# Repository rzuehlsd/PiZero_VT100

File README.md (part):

# VT100 Terminal Emulation on Raspberry Pi Zero W with Circle Bare Metal  Framework

## Table of Contents

- [Motivation](#motivation)
- [Regards](#regards)
- [Current Change Status](#current-change-status-2026-09-29)
- [License Statement](#license-statement)
- [Documentation Policy](#documentation-policy)
- [Software Implementation](#software-implementation)
  - [Scope and Goals](#scope-and-goals)
  - [Main Features](#main-features)
  - [Compile Environment Setup](#compile-environment-setup)
    - [Make Targets](#make-targets)
    - [macOS (tested)](#macos-tested)
    - [Important Note about Homebrew formulas](#important-note-about-homebrew-formulas)
  - [Configuration](#configuration)
    - [Configuration File: VT100.txt](#configuration-file-vt100txt)
    - [Available Options](#available-options)
      - [Configuration Summary](#configuration-summary)
      - [VT100 SETUP Screen A Parameter Mapping](#vt100-setup-screen-a-parameter-mapping-current-status)
      - [VT100 SETUP Screen B Parameter Mapping](#vt100-setup-screen-b-parameter-mapping-current-status)
      - [VT100 Extended Setup Dialog (F11)](#vt100-extended-setup-dialog-f11)
    - [DEC Local Mode (F10)](#dec-local-mode-f10)
    - [Example VT100.txt](#example-vt100txt)
  - [Circle Boot Files](#circle-boot-files)
  - [Display Orientation](#display-orientation)
  - [Debug and Logging](#debug-and-logging)
  - [WLAN Telnet and Host Mode](#wlan-telnet-and-host-mode)
    - [Log mode (WLAN diagnostics)](#log-mode-wlan-diagnostics)
    - [Shell-client mode (outbound raw TCP)](#shell-client-mode-outbound-raw-tcp)
    - [Host-side tooling reference](#host-side-tooling-reference)
    - [Auto-start shell-client mode](#auto-start-shell-client-mode)
    - [Strict mode separation](#strict-mode-separation)
  - [Internal VT100 Test Integration](#internal-vt100-test-integration)
  - [Initial Implementation Plan](#initial-implementation-plan)
  - [Templates](#templates)
  - [Overview on Escape Sequence Coverage](#overview-on-escape-sequence-coverage)
  - [VT100 Conformance Assessment](#vt100-conformance-assessment)
  - [Practical vttest Plan](#practical-vttest-plan)
  - [Troubleshooting](#troubleshooting)
    - [Build fails with stdint.h missing](#build-fails-with-fatal-error-stdinth-no-such-file-or-directory)
    - [VT100.txt changes have no effect](#vt100txt-changes-have-no-effect)
    - [Cannot connect to WLAN telnet console](#cannot-connect-to-wlan-telnet-console)
    - [Telnet shows logs but no shell-client traffic](#connected-via-telnet-but-only-logs-appear-no-shell-client-traffic)
    - [Shell-client uses UART instead of the remote host](#shell-client-mode-enabled-but-vt100-still-follows-uart-host)
    - [screen does not connect directly to TCP](#screen-does-not-connect-directly-to-tcp)
    - [Auto-enter host mode on every connect](#auto-enter-host-mode-on-every-connect)

## Motivation
My main motivation was that I wanted a terminal emulation for my VT100 replica (https://www.instructables.com/23-Scale-VT100-Terminal-Reproduction/) which I printed and assembled. I wanted something that could start within seconds, so a bare metal implementation on a Pi Zero seems to be the way to go. I looked into the PiGFX implementation by Filippo Bergamasco (https://github.com/fbergama/pigfx) and PiVT VT220 Emulator by Hans Hübner (https://github.com/hanshuebner/pivt). PiGFX for my taste was to much focused on reproducing vintage games on Z80 hardware or similar whereas PiVt was focused on VT220 with minimal configurability. Also the support for VT100 features like font stretching, double width fonts and double width double height fonts was missing in both implementations. 
So I decided to start my own VT100 Emulator journay and here is the result.

Below you see the original VT100 terminal (the color has turned to yellow over the years) and my 60% replica in a color that matches the original "oyster white" and some font examples:

<table>
  <tr>
    <td></td>
    <td></td>
  </tr>
  <tr>
    <td></td>
    <td></td>
  </tr>
</table>

The follwing link gives a very good view of the original VT100 from 1079:
- [Pictures of a VT100 from 1979](https://www.artstation.com/artwork/d05JgW)

The current VT100 terminal firmware turns a Raspberry Pi Zero W into a self-contained ANSI/VT100-compatible console. It boots straight into the terminal without Linux, using the Circle bare-metal framework for deterministic hardware access. The design targets headless benches and retro workstations that need a physical keyboard and display front-end for serial hosts.

This project also includes a PCB design to support enhanced features such as a buzzer, an RS-232 adapter, a Mini-DIN-6 adapter for MBC2-Z80, and power distribution for the Pi Zero, MBC2, and display, plus a backplate to mount the board inside a 60% VT100 replica designed by megardi.

My aim was to replicate the behaivior of a true VT100 as close as possible (vttest will show the final result ;-) ) and be able to mimic a VT52, VT220 and my favorite the VT320 in amber, also I did not replicate the small deviations of the VT220 or VT320 font sets. I got the original font definitions for a VT100 font from the ROM data used by Lars Brinkhoff to simulate a VT100 terminal in software on a Pi.

If you want a nearly 100% VT100 terminal simulation, please go for the VT100 simulation from Lars Brinkhoff (https://github.com/larsbrinkhoff/terminal-simulator). He simulates the complete VT100 hardware with original ROMs on a Raspberry Pi. The Pi executes the ROM by an 8080 emulator and simulates other components like video display with character generator ROM, settings NVRAM, Intel 8251 USART, and a keyboard matrix scanner. 

## Regards

Many thanks to Rene Stange (https://github.com/rsta2) for the creation of the Circle bare metal framework for Raspberry Pis. Without his work this project would not have been possible.

I take my hat off to the engineers a DEC which did a terrific job implementing the VT100 based on the technologies available at that time. They squeezed all functionality I implemented on a Pi with 1 GHz frequency and 512MB into a 8080A with 2Mhz, 8kB of ROM (including the original VT100 7x10 font) and 3kB of RAM. Granted, a lot of the features I had to implement in software were done with analog circuits, but I really feel embarressed by their skills.

## Current Change Status (2026-09-29)

- Hardware: the V2.3 design adds a GPIO7-controlled 5 V supply for a DIN6-connected SBC, BSS138 RX/TX level shifters, a 40 V / 2 A bridge rectifier, revised resistor pads, regulator notes, and a top-mount USB-A connector. The V2.3 board has not yet been manufactured or hardware-tested; the GPIO7 power test remains pending.
- Firmware: persistent `sbc_power` (default `0`) is available in the modern F11 setup and is applied at startup and when setup settings are saved with Enter. Setup-dialog behavior has been verified.

## License Statement 
Copyright (C) 2026 Ralf Zühlsdorff

This software and hardware design are released under the MIT License. You may use, copy, modify, merge, publish, distribute, sublicense, and/or sell copies of it, subject to including the copyright notice and permission notice in all copies or substantial portions.

## Documentation Policy

This project keeps documentation in a strict 4-document model:

- This `README.md` document provides the functional overview of the implemented software and user-facing operation guidance.
- [Architecture Overview](VT100/docs/VT100_Architecture.md) is the single technical architecture + implementation reference for developers.
- [Configuration Guide](VT100/docs/Configuration_Guide.md) contains all configuration guidance, split into user/operator and admin/developer parts.
- [Hardware Design](VT100/docs/Hardware.md) contains the KiCad design of the PCB and the OpenSCAD files for printing the backplate.

Generated API documentation is also published via GitHub Pages:

- [Doxygen HTML Documentation](https://rzuehlsd.github.io/PiZero_VT100/)

When implementation changes affect behavior, update these documents in lockstep and avoid introducing additional overlapping technical documents.

# Software Implementation

The application initialises USB keyboard input, the framebuffer, GPIO, UART, and WLAN within Circle and runs a cooperative task loop that keeps the terminal responsive even under heavy serial traffic. Classic aesthetics are preserved by rendering converted VT100 ROM fonts at 1024x768, while modern conveniences such as remote logging remain available.

The current renderer keeps terminal text, attributes, and DEC line-size state primarily in a shadow buffer and then projects that model onto the framebuffer through a dedicated projector task. During active smooth scrolling the projector stays on the incremental region-update path and defers any required catch-up full refresh until the animation completes. This makes state restore, scrolling, insert/delete operations, and external `vttest`-style screen rewrites behave against one consistent terminal model instead of depending on already-drawn pixels.

## Scope and Goals

- Provide a responsive VT100/ANSI terminal experience with integrated keyboard, framebuffer, and UART handling.
- Preserve classic look-and-feel through ROM-derived fonts, colour themes, and optional CRT-style scan lines.
- Offer configurable serial, display, audio, and logging behaviour via both on-device UI and SD-card files.
- Deliver flexible diagnostics through screen, file, and WLAN logging with remote telnet mirroring.
- Keep deployment simple: copy firmware, configuration files, and optional fonts onto an SD card and power the Pi.

## Main Features

- [x] USB keyboard input with Circle keymap support for multiple languages
- [x] Configurable line endings (LF, CRLF, CR)
- [x] Separate `VT100.txt` configuration file on the SD boot partition
- [x] Circle boot configuration via `cmdline.txt` and `config.txt`
- [x] Serial UART interface to host via RS232 and Mini-DIN-6 connector
- [x] Support for TCP/IP host connections
- [x] Framebuffer renderer supporting multiple VT fonts and colour themes
  - [x] DEC VT100 ROM 8x20 with scan-line simulation
  - [x] VT100 10x20 CRT-style font derived from DEC VT100 ROM Font
  - [x] VT100 10x20 solid font derived from DEC VT100 ROM Font
  - [x] DEC VT100 Special Graphics Character Set support (via `ESC ( 0` and `ESC ( B`)
  - [x] Dynamic Double-Width / Double-Height line attributes with DEC top/bottom-half semantics (`ESC #3/#4/#5/#6`)
  - [x] Visible SGR blink text rendering synchronized to the existing cursor blink cadence
  - [x] White, amber, and green on black simulate DEC monochrome terminals (VT100, VT220, VT320)
- [x] VT100 and ANSI escape sequence parser and renderer based on the VT-parse project
- [x] Configurable optional VT52 escape sequence support
- [x] 800 Hz buzzer with configurable volume for bell and key click feedback
- [x] Logging infrastructure with screen, file, and WLAN sinks
  - [x] Real-time debug output with formatted log messages
  - [x] WLAN debug output via telnet session
  - [x] WLAN split between incoming telnet log mode and outbound shell-client mode (current implementation)
  - [x] Shell-client mode can auto-connect from `host_id` or prompt locally for `IPv4[:port]`
  - [x] WLAN logging and shell-client mode successfully validated with local loopback and raw TCP helper tooling
- [x] GPIO16-controlled TX/RX swap to simulate Null Modem cables with straight DB9 cables
- [x] Configuration of system via VT100 Setup Screens A and B for supported parameters
- [x] Separate on-screen setup dialog covering the 24 persisted `VT100.txt` keys implemented there, including `smooth_scroll`, `smooth_scroll_ms`, `host_id`, and SBC power via `sbc_power` / GPIO7 (F11)

The following table gives an overview of implementation highlights:

| Area | Highlights |
| --- | --- |
| **Core Terminal** | ANSI/VT100 parser, ROM-derived fonts, shadow-buffer-first framebuffer renderer with DEC line-size control and visible blink attributes |
| **Input** | USB keyboard with F12 legacy setup, F11 modern setup, F10 local mode toggle, optional key click |
| **Serial** | Configurable UART baud rates, software flow control (XON/XOFF), GPIO16 TX/RX swap |
| **Display & Audio** | Runtime font switching, colour themes, buzzer tones, projector-owned smooth-scroll tuning, periodic status tasks |
| **Configuration** | SD-based `VT100.txt`, Circle `cmdline.txt`/`config.txt`, manual SD-card editing |
| **Logging** | Bitmask-controlled outputs (screen, file, WLAN), telnet console, timestamped files |
| **Networking** | WLAN bring-up with WPA supplicant, telnet banner showing `ip:2323` |
| **Deployment** | Makefile-driven build, SD card copy workflow, optional bootloader assets |

WLAN remote operation test status: WLAN logging mode and outbound shell-client mode have been successfully tested with local loopback and the helper workflows documented in `VT100/tools/README.md`.

And here are the results of the internal tests which could be switched on in VT100.txt config file:

## Compile Environment Setup

### Make Targets

The following table lists the implemented Make targets available from `VT100/Makefile` (including targets inherited via `../Rules.mk`) and their purpose.

| Target | Purpose |
| --- | --- |
| `all` | Default target; builds firmware image and copies it to `VT100/bin/kernel.img`. |
| `kernel.img` | Creates/refreshes local `kernel.img` symlink to `VT100/bin/kernel.img`. |
| `clean` | Removes generated build artifacts (`build/`, intermediate objects, map/list/elf/img outputs). |
| `docs` | Generates Doxygen documentation from `VT100/Doxyfile` into `VT100/docs/doxygen/`. |
| `docs_clean` | Removes generated Doxygen output directories/files under `VT100/docs/doxygen/`. |

This project needs a **complete bare-metal Arm GNU toolchain** (compiler + target C library headers like `stdint.h`).

### macOS (tested)

Install required host tools and the full Arm toolchain:

```bash
brew install make
brew install --cask gcc-arm-embedded
```

Configure Circle to use the full toolchain path explicitly:

```bash
cd /Users/ralf/Projekte/VT100_Circle
./configure -f -p /Applications/ArmGNUToolchain/15.2.rel1/arm-none-eabi/bin/arm-none-eabi-
```

Verify the compiler and header availability:

```bash
/Applications/ArmGNUToolchain/15.2.rel1/arm-none-eabi/bin/arm-none-eabi-gcc --version
printf '#include <stdint.h>\nint main(void){return 0;}\n' | \
    /Applications/ArmGNUToolchain/15.2.rel1/arm-none-eabi/bin/arm-none-eabi-gcc -x c - -c -o /tmp/vt100_stdint_test.o
```

Build steps:

```bash
cd /Users/ralf/Projekte/VT100_Circle
./makeall
cd VT100
make -j4
```

### Important Note about Homebrew formulas

The Homebrew formula `arm-none-eabi-gcc` may be built without target headers (`--without-headers`), which can cause errors like `fatal error: stdint.h: No such file or directory`. The `gcc-arm-embedded` cask provides the complete toolchain required by this project.

## Configuration

The VT100 terminal reads configuration from `VT100.txt` on the SD boot partition and supplements it with Circle boot parameters in `cmdline.txt` and firmware settings in `config.txt`/`config64.txt`.

### Configuration File: VT100.txt

Create or edit `VT100.txt` on the boot partition. The firmware loads it on startup, and settings can be changed either by manual edits or via the on-screen setup dialogs (F11/F12). See [VT100/bin/VT100.txt](VT100/bin/VT100.txt) for the shipping template.

### Available Options

#### Configuration Summary

| Key | Allowed values | Default | Notes |
| --- | --------------- | ------- | ----- |
| `baud_rate` | 50–921600 | 115200 | Host serial speed |
| `serial_bits` | 7/8 | 8 | UART data bits (SET-UP B Bits/Char) |
| `serial_parity` | 0–2 | 0 | UART parity (0=none, 1=even, 2=odd) |
| `background_color` | 0–3 | 0 | Palette: 0=black, 1=white, 2=amber, 3=green |
| `buzzer_volume` | 0–80 | 50 | Sets 800 Hz buzzer duty cycle (0 disables tone; values above 80 are clamped) |
| `cursor_blinking` | 0/1 | 0 | 1 enables blink animation |
| `cursor_type` | 0/1 | 0 | Cursor style (0=underline, 1=block) |
| `key_auto_repeat` | 0/1 | 1 | Enables or disables keyboard auto-repeat |
| `vt_test` | 0/1 | 0 | Run built-in VT test sequences |
| `vt52_mode` | 0/1 | 0 | Terminal mode: 0=ANSI (VT100), 1=VT52 |
| `font_selection` | 1–3 | 2 | Choose between 8x20, 10x20 CRT, 10x20 solid |
| `flow_control` | 0/1 | 0 | Software XON/XOFF UART flow control |
| `key_click` | 0/1 | 1 | Enables or disables key click feedback |
| `line_ending` | 0–2 | 0 | Enter key behaviour: 0=LF, 1=CRLF, 2=CR |
| `host_id` | String (IPv4[:port]) | empty | Default shell-client target used when `wlan_host_autostart=2` |
| `log_filename` | String (≤63 chars) | vt100.log | Used when file logging is active |
| `log_output` | 0–7 | 0 | 0=off, 1=screen, 2=file, 3=WLAN, 4=screen+file, 5=screen+WLAN, 6=file+WLAN, 7=all |
| `smooth_scroll` | 0/1 | 1 | Enables non-blocking smooth single-line scroll animation |
| `smooth_scroll_ms` | 10–500 | 170 | Sets the target duration per scrolled text line |
| `wrap_around` | 0/1 | 1 | Controls right-margin wrap (`1`) vs overwrite-at-last-column (`0`) |
| `repeat_delay_ms` | 250–1000 | 250 | Delay before auto-repeat starts |
| `repeat_rate_cps` | 2–20 | 10 | Characters per second once repeating |
| `margin_bell` | 0/1 | 0 | Rings bell 8 columns before right margin when enabled |
| `switch_txrx` | 0/1 | 0 | Drives GPIO16 high to swap wiring |
| `wlan_host_autostart` | 0–2 | 0 | Current implementation policy: 0=off, 1=log mode, 2=outbound shell-client mode |
| `text_color` | 0–3 | 1 | Foreground palette: 0=black, 1=white, 2=amber, 3=green |

On-screen configuration is available through the VT100 SET-UP dialogs A and B, opened with `F12`, and through an extended configuration dialog opened with `F11`. The extended dialog covers 23 persisted `VT100.txt` keys plus the runtime-applied visual settings; `flow_control`, `wrap_around`, and `margin_bell` remain on the legacy VT100-style `F12` path.

#### VT100 SETUP Screen A Parameter Mapping (current status)

The table below maps the current SET-UP A screen controls to firmware behavior.

| SET-UP A item | Corresponding config/runtime state | Implementation status |
| --- | --- | --- |
| Horizontal tab stops (per column) | Runtime tab-stop map via `CTConfig::SetTabStop()` / `CTConfig::IsTabStop()` | Implemented |
| Cursor movement in ruler (`Left`, `Right`, `Home`, `End`) | Tab edit cursor in SET-UP A ruler line | Implemented |
| Set/clear tab at current column (`T` / space) | Updates tab stop at current column | Implemented |
| Tab-stop persistence in `VT100.txt` | Not mapped to persisted file keys yet | Not implemented |

#### VT100 SETUP Screen B Parameter Mapping (current status)

The table below maps original VT100 SET-UP B terms to the current firmware configuration model.

| Tab group | Parameter name (VT100 docs) | Corresponding config param | Implementation status |
| --- | --- | --- | --- |
| 1 | Scroll | `smooth_scroll` (leftmost bit in group 1, mask `0x8`) | Implemented |
| 1 | Auto Repeat | `key_auto_repeat` (+ `repeat_delay_ms`, `repeat_rate_cps`) | Implemented |
| 1 | Screen | runtime-only (`screen_inverted`, not persisted) | Implemented |
| 1 | Cursor | `cursor_type` | Implemented |
| 2 | Bell | `margin_bell` (group 2 leftmost bit, mask `0x8`) | Implemented |
| 2 | Keyclick | `key_click` | Implemented |
| 2 | ANSI/VT52 | `vt52_mode` | Implemented |
| 2 | Auto XON/XOFF | `flow_control` (group 2 rightmost shown bit, mask `0x1`) | Implemented |
| 3 | US/UK # | N/A | Not implemented |
| 3 | Wraparound | `wrap_around` (group 3 second bit from left, mask `0x4`) | Implemented |
| 3 | New Line | `line_ending` | Implemented |
| 3 | Interlace | N/A | Not implemented |
| 4 | Parity Sense | `serial_parity` (1=even, 2=odd when parity enabled) | Implemented |
| 4 | Parity | `serial_parity` (0=none, 1/2=enabled) | Implemented |
| 4 | Bits/Char | `serial_bits` (7/8) | Implemented |
| 4 | Power | N/A | Not implemented |
| — | T SPEED (Transmit Speed) | `baud_rate` | Implemented |
| — | R SPEED (Receive Speed) | Follows `baud_rate` (TX speed) | Always follows transmit speed |

#### VT100 Extended Setup Dialog (F11)

Press `F11` to open the extended setup dialog. The dialog uses DEC special graphics box drawing, keeps the active terminal color/font theme, uses a centered normal-width title, and shows a three-column `parameter` / `value` / `description` view for the 23 persisted `VT100.txt` keys exposed there, including `smooth_scroll`, `smooth_scroll_ms`, and `host_id`. The remaining persisted keys `flow_control`, `wrap_around`, and `margin_bell` stay mapped to the VT100-compatible `F12` setup flow. Before the overlay takes over the screen, the renderer aborts any active smooth-scroll animation and forces a stable projector refresh so the dialog always starts from a complete framebuffer state. Press `F12` for the legacy VT100 setup screens; their title renders as a true two-line DEC double-height header with `TO EXIT PRESS "SET-UP"` directly below it, matching the original VT100 layout more closely.

Controls:

- `Up` / `Down`: select parameter row
- `Left` / `Right`: change selected value
- `Return`: save to runtime + `VT100.txt` and exit
- `Esc`: cancel changes and exit

Runtime apply on `Return` (current firmware):

- Immediate runtime apply: renderer visuals (`text_color`, `background_color`, `font_selection`, cursor type/blink, VT52 mode, `smooth_scroll`, `smooth_scroll_ms`) and HAL settings (`buzzer_volume`, `switch_txrx`).
- Persisted and used by runtime logic without dedicated re-init: `line_ending`, `key_click`, `key_auto_repeat`.
- Persisted (applied on subsystem init / reconnect / reboot): serial framing (`baud_rate`, `serial_bits`, `serial_parity`), keyboard repeat timing (`repeat_delay_ms`, `repeat_rate_cps`), logging targets (`log_output`, `log_filename`), and WLAN host settings (`wlan_host_autostart`, `host_id`).
- Persisted legacy-setup-only keys: `flow_control`, `wrap_around`, and `margin_bell` are edited through `F12`, not through the modern `F11` table.
- While a setup dialog is visible, cooked and raw keyboard events are routed into `CTSetup`, queued in a small FIFO, and then processed in the setup task context so redraws remain stable even when the shell-client connection is active.

### DEC Local Mode (F10)

The DEC feature to toggle the terminal between local (not connected to host) and line (connected to host) mode can be triggered by pressing `F10`.

- `ON`: keyboard input is looped directly to the renderer (local echo), and host output is not sent over UART/TCP.
- `OFF`: keyboard input follows the normal host path again.

The terminal prints a short status line (`VT100 local mode ON/OFF`) when toggled.

### Example VT100.txt

Most of the configurations can be defined in the file VT100.txt on the root volume of the boot SD. The following sections give a summary:

```ini
# VT100 Terminal Configuration File
# Place this file as VT100.txt on the SD card boot partition.
# Values below match firmware defaults.

# --- Serial communication ---
# Host serial speed in bits per second
baud_rate=115200

# UART framing:
# serial_bits: 7 or 8
# serial_parity: 0=None, 1=Even, 2=Odd
serial_bits=8
serial_parity=0

# --- Keyboard / line handling ---
# line_ending: 0=LF, 1=CRLF, 2=CR
line_ending=0

# key_auto_repeat: 0=off, 1=on
key_auto_repeat=1

# smooth_scroll: 0=off, 1=on
smooth_scroll=1

# smooth_scroll_ms: 10..500 milliseconds per text line
smooth_scroll_ms=170

# wrap_around: 0=overwrite at last column, 1=wrap to next line
wrap_around=1

# flow_control: 0=off, 1=software XON/XOFF
flow_control=0

# Delay before repeat starts (milliseconds: 250..1000)
repeat_delay_ms=250

# Repeat rate (characters per second: 2..20)
repeat_rate_cps=10

# key_click: 0=off, 1=on
key_click=1

# --- Terminal mode / display ---
# vt52_mode: 0=ANSI (VT100), 1=VT52
vt52_mode=0

# cursor_type: 0=underline, 1=block
cursor_type=0

# cursor_blinking: 0=steady, 1=blinking
cursor_blinking=0

# vt_test: 0=off, 1=on
vt_test=0

# font_selection: 1=8x20, 2=10x20 CRT, 3=10x20 solid
font_selection=2

# Palette indices: 0=black, 1=white, 2=amber, 3=green
text_color=1
background_color=0

# --- Sound / wiring ---
# buzzer_volume: 0..80 (percent duty cycle)
buzzer_volume=50

# margin_bell: 0=off, 1=ring 8 columns before right margin
margin_bell=0

# switch_txrx: 0=normal wiring, 1=swapped via GPIO16
switch_txrx=0

# --- Logging ---
# log_output:
# 0=off
# 1=screen
# 2=file
# 3=wlan
# 4=screen+file
# 5=screen+wlan
# 6=file+wlan
# 7=screen+file+wlan
log_output=0

# wlan_host_autostart: 0=off, 1=remote log mode, 2=outbound shell-client mode
wlan_host_autostart=0

# host_id: default shell-client target when wlan_host_autostart=2
# Format: IPv4[:port] (e.g. 192.168.2.10 or 192.168.2.10:2323). Leave empty to prompt.
host_id=

# Log file name (max 63 chars)
log_filename=vt100.log
```

## Circle Boot Files

- `cmdline.txt` — Parsed by Circle during boot. Keep options on one line, e.g. `logdev=tty1 loglevel=4 width=1024 height=768 keymap=DE`.
- `config.txt` / `config64.txt` — Raspberry Pi firmware settings. The template applies `dtoverlay=miniuart-bt`, `enable_uart=1`, and `display_hdmi_rotate=2` for the upside-down LCD in the replica enclosure.

Both templates live in `VT100/bin` alongside the firmware image and WLAN support files.

## Display Orientation

In the 60% VT100 replica, depending on the specific model used, the 1024x768 LCD can hide part of the first line and the left-most characters behind the bezel when mounted in the natural orientation. Mounting the panel upside down resolves the mechanical clearance issue. Rotate the output by 180° by adding the following firmware setting to the active `config.txt`/`config64.txt`:

```ini
display_hdmi_rotate=2
```

This rotates the HDMI output 180° at the firmware level so the framebuffer keeps its normal coordinate system without extra rendering adjustments.

## Debug and Logging

The terminal ships with a logging subsystem that mirrors messages to any combination of screen, SD card file, and WLAN telnet session:

- Smart fallback selects a working sink during early boot and transitions seamlessly once the framebuffer is ready.
- Messages use familiar prefixes (`[NOTE]`, `[WARN]`, `[ERROR]`) with file/line metadata to simplify troubleshooting.
- Screen logging integrates with the terminal view without breaking VT100 escape handling.
- WLAN logging announces readiness with `WLAN ready: telnet <ip>:2323`; connect via telnet to monitor remotely.
- Outbound shell-client integration over raw TCP is available for host-side helpers and interactive shells.

Refer to `VT100/docs/VT100_Architecture.md` for technical architecture and implementation details, and `VT100/docs/Configuration_Guide.md` for runtime controls and configuration.

For the architecture and lifecycle model of WLAN log mode and host mode separation, see `VT100/docs/VT100_Architecture.md` (section 8.3).
For host-side helper scripts and character-mode client recommendations, see `VT100/tools/README.md`.

## WLAN Telnet and Host Mode

This firmware currently supports two WLAN behaviors that share the same raw TCP port (`2323`) but serve different roles:

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
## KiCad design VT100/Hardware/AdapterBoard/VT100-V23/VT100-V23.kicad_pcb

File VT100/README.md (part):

# VT100 Terminal Emulation on Raspberry Pi Zero W with Circle Bare Metal  Framework

## Motivation
My main motivation was that I wanted a terminal emulation for my VT100 replica (https://www.instructables.com/23-Scale-VT100-Terminal-Reproduction/) which I printed and assembled. I wanted something that could start within seconds, so a bare metal implementation on a Pi Zero seems to be the way to go. I looked into the PiGFX implementation by Filippo Bergamasco (https://github.com/fbergama/pigfx) and PiVT VT220 Emulator by Hans Hübner (https://github.com/hanshuebner/pivt). PiGFX for my taste was to much focused on reproducing vintage games on Z80 hardware or similar whereas PiVt was focused on VT220 with minimal configurability. Also the support for VT100 features like font stretching, double width fonts and double width double height fonts was missing in both implementations. 
So I decided to start my own VT100 Emulator journay and here is the result.

Below you see the original VT100 terminal (the color has turned to yellow over the years) and my 60% replica in a color that matches the original "oyster white" and some font examples:

<table>
  <tr>
    <td></td>
    <td></td>
  </tr>
  <tr>
    <td></td>
    <td></td>
  </tr>
</table>

The current VT100 terminal firmware turns a Raspberry Pi Zero W into a self-contained ANSI/VT100-compatible console. It boots straight into the terminal without Linux, using the Circle bare-metal framework for deterministic hardware access. The design targets headless benches and retro workstations that need a physical keyboard and display front-end for serial hosts.

This project also includes a PCB design to support enhanced features such as a buzzer, an RS-232 adapter, a Mini-DIN-6 adapter for MBC2-Z80, and power distribution for the Pi Zero, MBC2, and display, plus a backplate to mount the board inside a 60% VT100 replica designed by megardi.

My aim was to replicate the behaivior of a true VT100 as close as possible (vttest will show the final result ;-) ) and be able to mimic a VT52, VT220 and my favorite the VT320 in amber, also I did not replicate the small deviations of the VT220 or VT320 font sets. I got the original font definitions for a VT100 font from the ROM data used by Lard Brinkhoff to simulate a VT100 terminal in software on a Pi.

If you want a nearly 100% VT100 terminal simulation, please go for the VT100 simulation from Lars Brinkhoff (https://github.com/larsbrinkhoff/terminal-simulator). He simulates the complete VT100 hardware with original ROMs on a Raspberry Pi. The Pi executes the ROM by an 8080 emulator and simulates other components like video display with character generator ROM, settings NVRAM, Intel 8251 USART, and a keyboard matrix scanner. 

## Regards

Many thanks to Rene Stange (https://github.com/rsta2) for the creation of the Circle bare metal framework for Raspberry Pis. Without his work this project would not have been possible.

I take my hat off to the engineers a DEC which did a terrific job implementing the VT100 based on the technologies available at that time. They squeezed all functionality I implemented on a Pi with 1 GHz frequency and 512MB into a 8080A with 2Mhz, 8kB of ROM (including the original VT100 7x10 font) and 3kB of RAM. Granted, a lot of the features I had to implement in software were done with analog circuits, but I really feel embarressed by their skills.

## License Statement 
Copyright (C) 2026 Ralf Zühlsdorff

This software and hardware design are released under the MIT License. You may use, copy, modify, merge, publish, distribute, sublicense, and/or sell copies of it, subject to including the copyright notice and permission notice in all copies or substantial portions.

## Documentation Policy

This project keeps documentation in a strict 4-document model:

- This `README.md` document provides the functional overview of the implemented software and user-facing operation guidance.
- [Architecture Overview](docs/VT100_Architecture.md) is the single technical architecture + implementation reference for developers.
- [Configuration Guide](docs/Configuration_Guide.md) contains all configuration guidance, split into user/operator and admin/developer parts.
- [Hardware Design](docs/Hardware.md) contains the KiCad design of the PCB and the OpenSCAD files for printing the backplate.

When implementation changes affect behavior, update these documents in lockstep and avoid introducing additional overlapping technical documents.

# Software Implementation

The application initialises USB keyboard input, the framebuffer, GPIO, UART, and WLAN within Circle and runs a cooperative task loop that keeps the terminal responsive even under heavy serial traffic. Classic aesthetics are preserved by rendering converted VT100 ROM fonts at 1024x768, while modern conveniences such as remote logging remain available.

## Scope and Goals

- Provide a responsive VT100/ANSI terminal experience with integrated keyboard, framebuffer, and UART handling.
- Preserve classic look-and-feel through ROM-derived fonts, colour themes, and optional CRT-style scan lines.
- Offer configurable serial, display, audio, and logging behaviour via both on-device UI and SD-card files.
- Deliver flexible diagnostics through screen, file, and WLAN logging with remote telnet mirroring.
- Keep deployment simple: copy firmware, configuration files, and optional fonts onto an SD card and power the Pi.

## Main Features

- [x] USB keyboard input with Circle keymap support for multiple languages
- [x] Configurable line endings (LF, CRLF, CR)
- [x] Separate `VT100.txt` configuration file on the SD boot partition
- [x] Circle boot configuration via `cmdline.txt` and `config.txt`
- [x] Serial UART interface to host via RS232 and Mini-DIN-6 connector
- [x] Support for TCP/IP host connections
- [x] Framebuffer renderer supporting multiple VT fonts and colour themes
  - [x] DEC VT100 ROM 8x20 with scan-line simulation
  - [x] VT100 10x20 CRT-style font derived from DEC VT100 ROM Font
  - [x] VT100 10x20 solid font derived from DEC VT100 ROM Font
  - [x] DEC VT100 Special Graphics Character Set support (via `ESC ( 0` and `ESC ( B`)
  - [x] Dynamic Double-Width / Double-Height glyph scaling for all fonts
  - [x] White, amber, and green on black simulate DEC monochrome terminals (VT100, VT220, VT320)
- [x] VT100 and ANSI escape sequence parser and renderer based on the VT-parse project
- [x] Configurable optional VT52 escape sequence support
- [x] 800 Hz buzzer with configurable volume for bell and key click feedback
- [x] Logging infrastructure with screen, file, and WLAN sinks
  - [x] Real-time debug output with formatted log messages
  - [x] WLAN debug output via telnet session
  - [x] WLAN host mode to integrate remote hosts via tcp/ip
- [x] GPIO16-controlled TX/RX swap to simulate Null Modem cables with straight DB9 cables
- [x] Configuration of system via VT100 Setup Screens A and B for supported parameters
- [x] Separate on-screen setup dialog covering all file-based configuration parameters (F11)

The following table gives an overview of implementation highlights:

| Area | Highlights |
| --- | --- |
| **Core Terminal** | ANSI/VT100 parser, ROM-derived fonts, framebuffer renderer with cursor control |
| **Input** | USB keyboard with F12 legacy setup, F11 modern setup, F10 local mode toggle, optional key click |
| **Serial** | Configurable UART baud rates, software flow control (XON/XOFF), GPIO16 TX/RX swap |
| **Display & Audio** | Runtime font switching, colour themes, buzzer tones, periodic status tasks |
| **Configuration** | SD-based `VT100.txt`, Circle `cmdline.txt`/`config.txt`, manual SD-card editing |
| **Logging** | Bitmask-controlled outputs (screen, file, WLAN), telnet console, timestamped files |
| **Networking** | WLAN bring-up with WPA supplicant, telnet banner showing `ip:2323` |
| **Deployment** | Makefile-driven build, SD card copy workflow, optional bootloader assets |

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
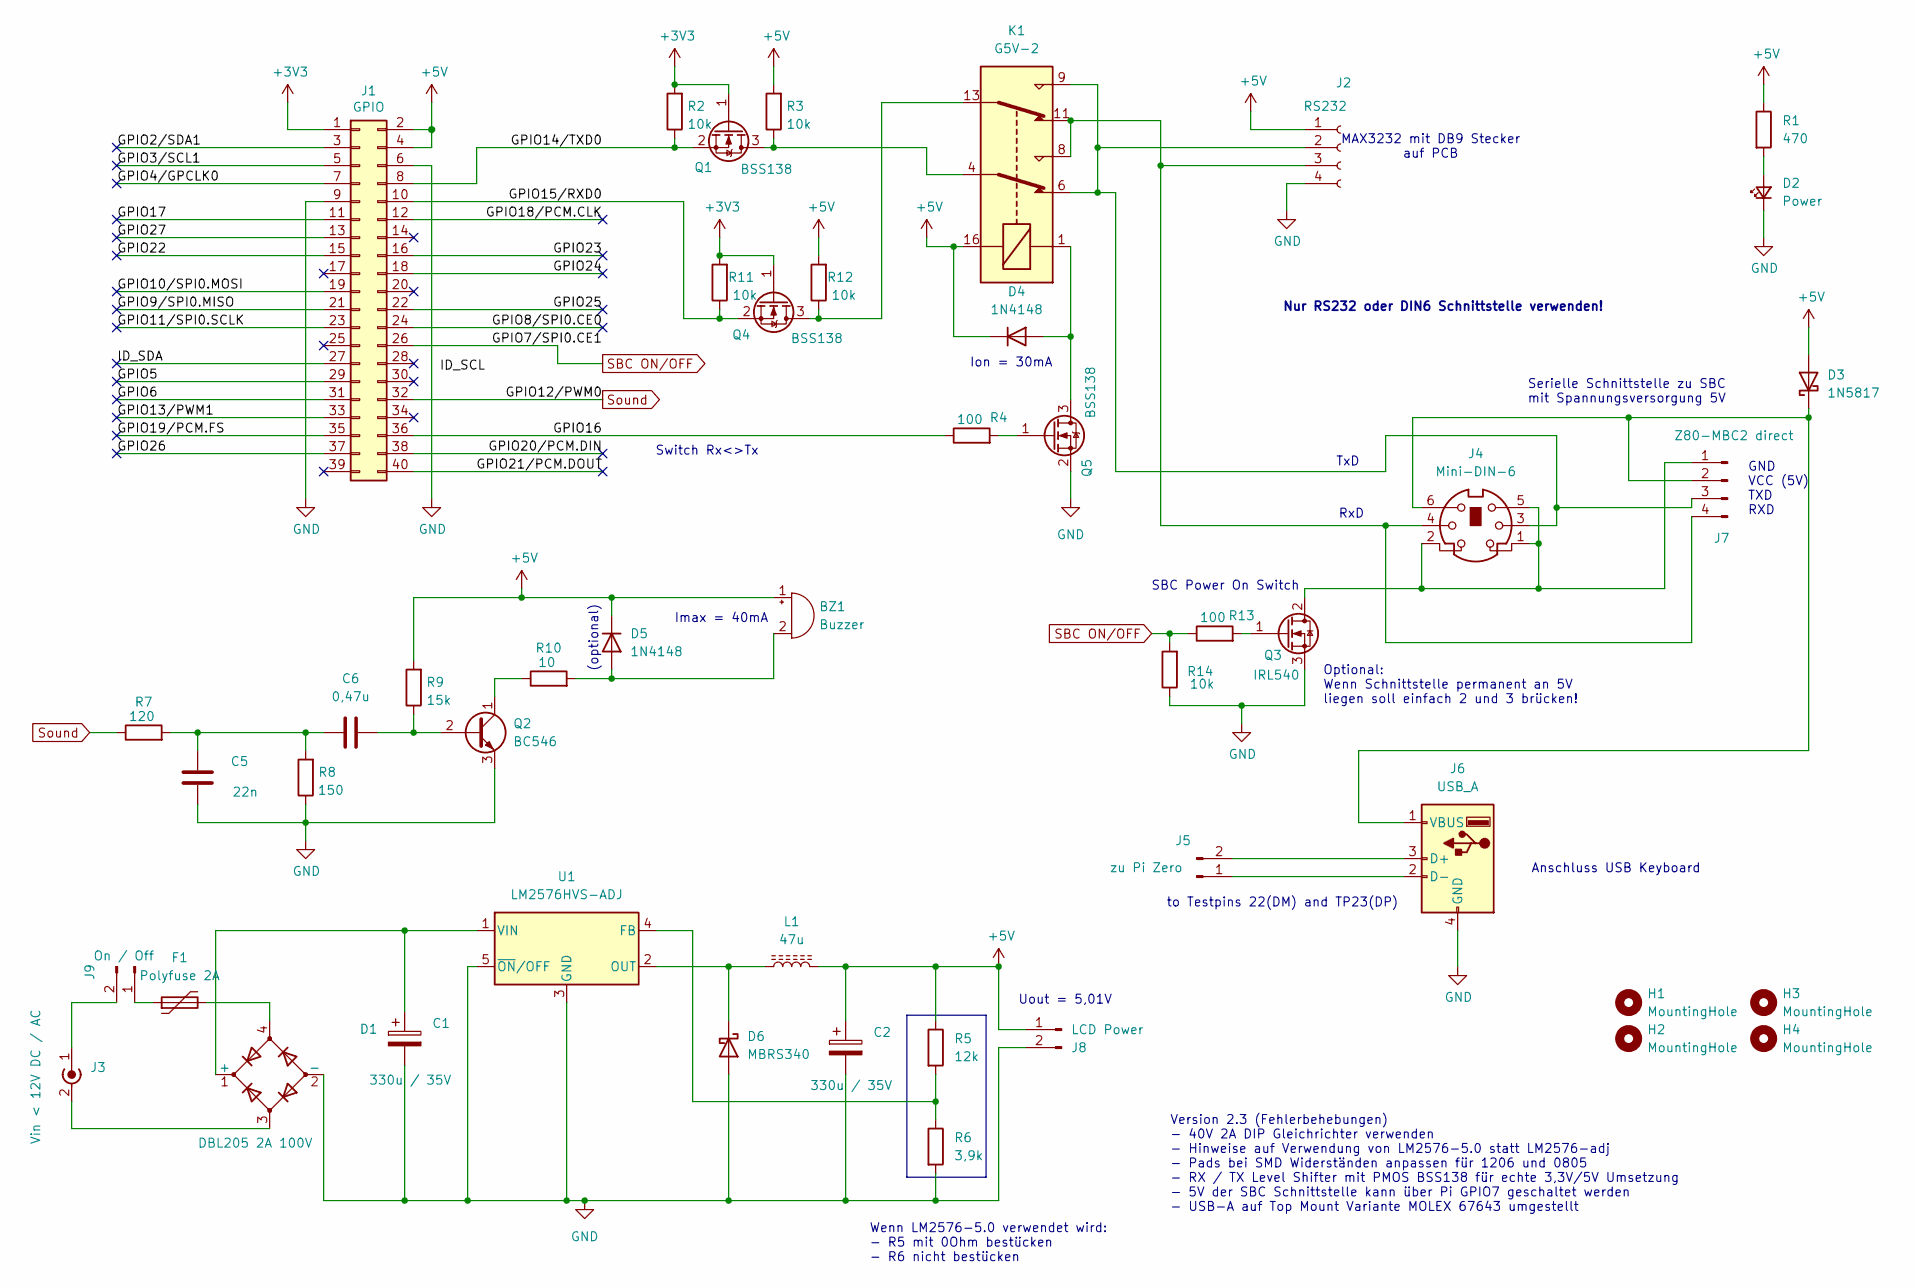
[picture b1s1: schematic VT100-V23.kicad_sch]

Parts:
BZ1: Buzzer; MagneticBuzzer_ProSignal_ABI-009-RC
C1, C2: 330u / 35V; CP_Elec_10x10
C5: 22n; C_0805_2012Metric_Pad1.18x1.45mm_HandSolder
C6: 0,47u; C_0805_2012Metric_Pad1.18x1.45mm_HandSolder
D1: DBL205 2A 100V; Diode_Bridge_DIP-4_W7.62mm_P5.08mm
D2: Power; LED_D3.0mm
D3: 1N5817; D_DO-15_P12.70mm_Horizontal
D4, D5: 1N4148; D_A-405_P10.16mm_Horizontal
D6: MBRS340; D_SMC
F1: Polyfuse 2A; Fuse_Littelfuse-LVR200
H1, H2, H3, H4: MountingHole; MountingHole_3.2mm_M3
J1: GPIO; PinSocket_2x20_P2.54mm_Vertical
J2: RS232; PinSocket_1x04_P2.54mm_Vertical
J3: Vin < 12V DC / AC; BarrelJack_GCT_DCJ200-10-A_Horizontal
J4: Mini-DIN-6; J_Mini-DIN-6
J5: zu Pi Zero; PinHeader_1x02_P2.54mm_Vertical
J6: USB_A; USB_A_Molex_67643_Horizontal
J7: Z80-MBC2 direct; PinHeader_1x04_P2.54mm_Vertical
J8: LCD Power; PinHeader_1x02_P2.54mm_Vertical
J9: On / Off; PinHeader_1x02_P2.54mm_Vertical
K1: G5V-2; Relay_DPDT_Omron_G5V-2
L1: 47u; L_Fastron_PISN
Q1, Q4, Q5: BSS138; SOT-23
Q2: BC546; TO-92_Wide
Q3: IRL540; TO-220-3_Vertical
R1: 470; R_Axial_DIN0207_L6.3mm_D2.5mm_P10.16mm_Horizontal
R2, R3, R11, R12, R14: 10k; R_0805_2012Metric_Pad1.20x1.40mm_HandSolder
R4, R13: 100; R_0805_2012Metric_Pad1.20x1.40mm_HandSolder
R5: 12k; R_1206_3216Metric_Pad1.30x1.75mm_HandSolder
R6: 3,9k; R_1206_3216Metric_Pad1.30x1.75mm_HandSolder
R7: 120; R_0805_2012Metric_Pad1.20x1.40mm_HandSolder
R8: 150; R_0805_2012Metric_Pad1.20x1.40mm_HandSolder
R9: 15k; R_0805_2012Metric_Pad1.20x1.40mm_HandSolder
R10: 10; R_0805_2012Metric_Pad1.20x1.40mm_HandSolder
U1: LM2576HVS-ADJ; TO-263-5_TabPin3

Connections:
+3V3: J1.1, Q1.1 (G), Q4.1 (G), R2.2, R11.2
+5V: BZ1.1 (+), C2.1, D3.2 (A), D4.1 (K), D5.1 (K), J1.2, J1.4, J2.1, J8.1, K1.16, L1.2, R1.1, R3.2, R5.1, R9.2, R12.2
/GPIO2/SDA1: J1.3
/GPIO3/SCL1: J1.5
/GPIO4/GPCLK0: J1.7
/GPIO5: J1.29
/GPIO6: J1.31
/GPIO8/SPI0.CE0: J1.24
/GPIO9/SPI0.MISO: J1.21
/GPIO10/SPI0.MOSI: J1.19
/GPIO11/SPI0.SCLK: J1.23
/GPIO13/PWM1: J1.33
/GPIO14/TXD0: J1.8, Q1.2 (S), R2.1
/GPIO15/RXD0: J1.10, Q4.2 (S), R11.1
/GPIO16: J1.36, R4.1
/GPIO17: J1.11
/GPIO18/PCM.CLK: J1.12
/GPIO19/PCM.FS: J1.35
/GPIO20/PCM.DIN: J1.38
/GPIO21/PCM.DOUT: J1.40
/GPIO22: J1.15
/GPIO23: J1.16
/GPIO24: J1.18
/GPIO25: J1.22
/GPIO26: J1.37
/GPIO27: J1.13
/ID_SDA: J1.27
GND: C1.2, C2.2, C5.2, D1.2 (-), D2.1 (K), D6.2 (A), J1.6, J1.9, J2.4, J6.4 (GND), J8.2, Q2.3 (E), Q3.3 (S), Q5.2 (S), R6.2, R8.1, R14.1, U1.3 (GND), U1.5 (~ON/OFF)
unnamed: BZ1.2 (-), D5.2 (A), R10.2
unnamed: C5.1, C6.1, R7.2, R8.2
unnamed: C1.1, D1.1 (+), U1.1 (VIN)
unnamed: D1.4, F1.2
unnamed: D2.2 (A), R1.2
unnamed: D3.1 (K), J4.6, J6.1 (VBUS), J7.2
unnamed: D4.2 (A), K1.1, Q5.3 (D)
unnamed: D6.1 (K), L1.1, U1.2 (OUT)
unnamed: J2.2, J4.3, J7.3, K1.6, K1.9
unnamed: J2.3, J4.4, J7.4, K1.8, K1.11
unnamed: D1.3, J3.2 (Ext)
unnamed: J3.1 (In), J9.2
unnamed: J5.1, J6.2 (D-)
unnamed: J5.2, J6.3 (D+)
unnamed: J4.1, J4.2, J4.5, J7.1, Q3.2 (D)
unnamed: F1.1, J9.1
unnamed: K1.4, Q1.3 (D), R3.1
unnamed: C6.2, Q2.2 (B), R9.1
unnamed: Q2.1 (C), R10.1
unnamed: Q3.1 (G), R13.2
unnamed: K1.13, Q4.3 (D), R12.1
unnamed: Q5.1 (G), R4.2
unnamed: R5.2, R6.1, U1.4 (FB)
SBC ON/OFF: J1.26, R13.1, R14.2
Sound: J1.32, R7.1

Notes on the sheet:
Imax = 40mA
TxD
RxD
Wenn LM2576-5.0 verwendet wird: - R5 mit 0Ohm bestücken - R6 nicht bestücken
Version 2.3 (Fehlerbehebungen) - 40V 2A DIP Gleichrichter verwenden - Hinweise auf Verwendung von LM2576-5.0 statt LM2576-adj - Pads bei SMD Widerständen anpassen für 1206 und 0805 - RX / TX Level Shifter mit PMOS BSS138 für echte 3,3V/5V Umsetzung - 5V der SBC Schnittstelle kann über Pi GPIO7 gesc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
Ion = 30mA
(optional)
MAX3232 mit DB9 Stecker auf PCB
Anschluss USB Keyboard
Nur RS232 oder DIN6 Schnittstelle verwenden!
Serielle Schnittstelle zu SBC mit Spannungsversorgung 5V
SBC Power On Switch
Switch Rx<>Tx
Optional: Wenn Schnittstelle permanent an 5V liegen soll einfach 2 und 3 brücken!
to Testpins 22(DM) and TP23(DP)
GND VCC (5V) TXD RXD
Uout = 5,01V

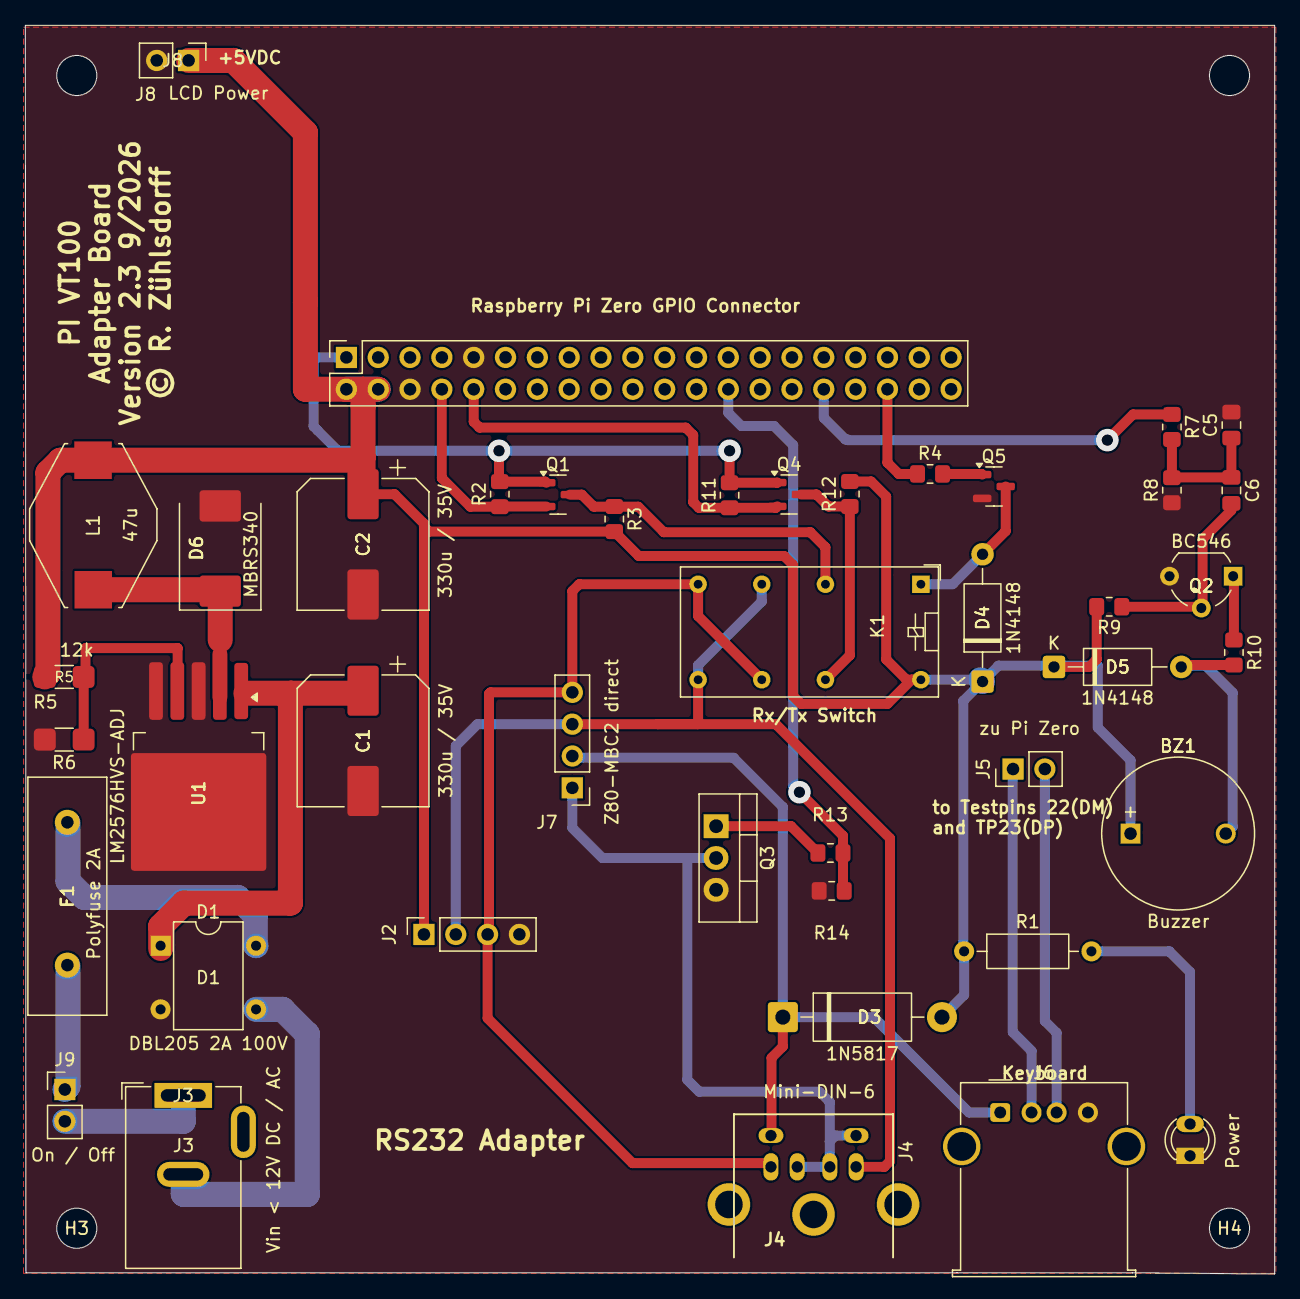
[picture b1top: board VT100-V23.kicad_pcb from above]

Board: 2 copper layers, 99.7 x 99.6 mm, 47 parts (0 on the bottom side), 31 nets.

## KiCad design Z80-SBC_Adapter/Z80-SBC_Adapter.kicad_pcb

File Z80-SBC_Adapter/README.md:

# Adapterplatine für MBC2-Z80 Board
<div align="center">
RZ 9/2015
</br>
</br>
</div>

Das MBC2 Board benötigt eine Adapterplatine für den Anschluss an das VT100 Terminal Board.
Das Board ist auf einer Trägerplatine aufgebaut, die mit 2 Distanzstücken oberhalb der MBC2 Platine montiert wird. Die elektrischen Verbindungen werden über die auf dem MBC2 vorhandene Steckerbuchse für den Seriell to USB Adapter hergestellt.

Auf der Adapterplatine sind die folgenden Funktionen realisiert:

- 5VDC Netzteil zur Spannungsversorgung des MBC2 über ein Steckernetzteil (7 - 9 VAC oder DC Spannung)
- Mini DIN6 Buchse für die Verbindung mit dem Terminal Board. Über diesen Stecker kann auch der MBC2 mit einer 5VDC Betriebsspannung versorgt werden.
- 4 poliger Pin Header zum direkten Anschluss des MBC2 über Jumper Kabel mit der Terminal Platine
- USB to Seriall Adapter für direkten Anschluss an Mac
- LED zu Anzeige der Betriebsspannung
- Ein/Aus Schalter

To Dos:

- [ ] Die auf dem MBC2 Board verbauten horizontalen Microschalter müssen durch vertikale Microschalter ersetzt werden, um auch außerhalb eines Gehäuses bedienbar zus ein
- [x] Konstruktion eines kleinen Gehäuses für den 3D Druck
- [x] Das Layout wurde komplett auf die Rückseite verlegt
- [ ] Verzögertes Einschalten implementieren, da Probleme mit VT100 falls zur gleichen Zeit Spannung anliegt -> prüfen!

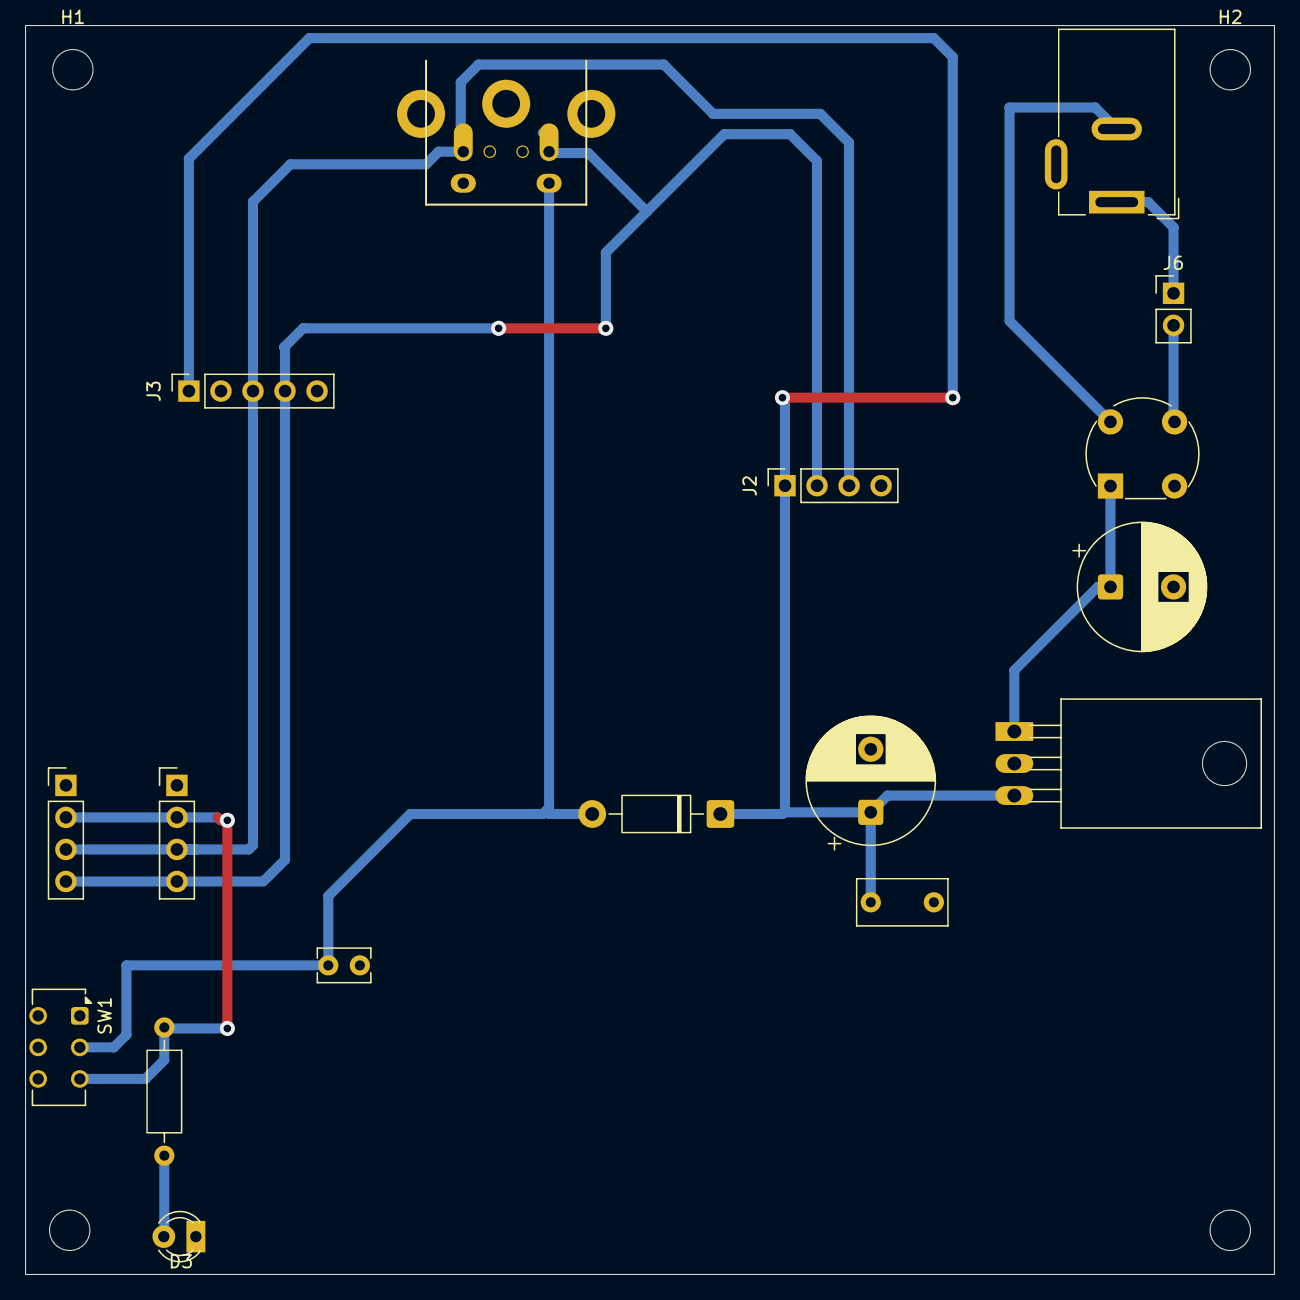
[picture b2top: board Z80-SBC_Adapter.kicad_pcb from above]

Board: 2 copper layers, 99.0 x 99.0 mm, 21 parts (0 on the bottom side), 11 nets.

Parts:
C1: 0.1u; C_Rect_L4.0mm_W2.5mm_P2.50mm
C2: 100u / 16V; CP_Radial_D10.0mm_P5.00mm
C3: 47u / 16V; CP_Radial_D10.0mm_P5.00mm
C4: 0.1u; C_Rect_L7.0mm_W3.5mm_P5.00mm
D1: 25V / 500mA; Diode_Bridge_Round_D8.9mm
D2: 1N5817; D_DO-41_SOD81_P10.16mm_Horizontal
D3: ON/OFF; LED_D3.0mm
H1, H1#2, H2, H2#2: MountingHole; MountingHole_3.2mm_M3
J1: Z80-MBC2 direct; PinHeader_1x04_P2.54mm_Vertical
J2: RS232 Adapterplatine; PinSocket_1x04_P2.54mm_Vertical
J3: USB-Serial-Adapter Board; PinSocket_1x05_P2.54mm_Vertical
J4: Mini-DIN-6; J_Mini-DIN-6
J5: 5,4x2,1mm 7 - 9V DC/AC; BarrelJack_Wuerth_6941xx301002
J6: Power on / off; PinHeader_1x02_P2.54mm_Vertical
J7: Z80-MBC2 Board; PinHeader_1x04_P2.54mm_Vertical
R1: 470; R_Axial_DIN0207_L6.3mm_D2.5mm_P10.16mm_Horizontal
SW1: On Off; SW_CK_JS202011AQN_DPDT_Angled
U1: L7805; TO-220-3_Horizontal_TabDown

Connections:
5VDC: C3.1, C4.1, D2.1 (K), J2.1, J3.1, U1.3 (OUT)
GND: C1.2, C2.2, C3.2, C4.2, D1.2 (-), D3.1 (K), J1.1, J2.4, J3.2, J4.1, J4.2, J4.5, J7.1, SW1.4 (A), SW1.5 (B), SW1.6 (C), U1.2 (GND)
unnamed: C2.1, D1.1 (+), U1.1 (IN)
unnamed: C1.1, D2.2 (A), J4.6, SW1.2 (B)
unnamed: D3.2 (A), R1.2
unnamed: J1.2, J7.2, R1.1, SW1.3 (C)
unnamed: J1.3, J2.3, J3.3, J4.3, J7.3
unnamed: J1.4, J2.2, J3.4, J4.4, J7.4
unnamed: D1.4, J5.2
unnamed: J5.1, J6.1
unnamed: D1.3, J6.2

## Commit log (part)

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2025-09-01 Platine erfolgreich getestet, Modifikationen im Design berücksichtigt und beschrieben.
2025-09-01 Erweiterung der Beschreibung
2025-09-15 Adapterplatine überarbeitet
2025-09-15 Umschalter TxD / RxD über Relais
2025-09-15 LM350 eingebaut in Design
2025-09-17 Layout geändert bei Adapterplatine MSBC-z80
2026-02-18 Initial publish: VT100 app + Circle submodule
2026-02-18 Repository clean up
2026-02-18 Agents file hinzugefügt
2026-02-18 CI: publish Doxygen docs via GitHub Pages
    - Add GitHub Actions workflow to build and deploy VT100 Doxygen HTML.
    - Fix Doxyfile mainpage/input path to root README after README move.
    - Add README link to published Pages documentation URL.
    - Update daily changelog for 2026-02-18.
    - Validation: make docs passed in VT100/.
2026-02-18 Docs: mirror README image paths into Doxygen output
    - Extend VT100 Makefile docs target to copy docs/images into docs/doxygen/html/VT100/docs/images.
    - Fix root README image rendering on generated Doxygen main page.
    - Update daily changelog for 2026-02-18.
    - Validation: make docs; README_IMAGE_REFS=5, MISSING_IN_HTML_TREE=0.
2026-02-18 Docs: restore Mermaid rendering in architecture markdown
    - Add standard fenced mermaid blocks for dependency and sequence diagrams.
    - Keep existing Doxygen htmlonly mermaid blocks for generated HTML docs.
    - Update daily changelog for 2026-02-18.
    - Validation: make docs passed.
2026-02-18 Docs: fix Hardware.md image paths
    - Update hardware markdown image sources to images/... under VT100/docs/images.
    - Restore image rendering in Git markdown and generated Doxygen pages.
    - Add 2026-02-19 changelog entry.
    - Validation: make docs passed and all 4 image paths resolve.
2026-02-20 VT100: harmonize WLAN mode docs and add separation roadmap
    Align README/Configuration/Architecture/Testplan wording to log mode vs host mode.
    Add phased WLAN mode separation plan with migration policy proposal.
    Update daily changelog and validate docs via make docs.
2026-02-20 VT100: ignore local generated artifacts
    Add ignore rules for local build outputs and generated doxygen separation-page artifact.
    Keeps working tree clean after local builds/docs generation without touching tracked source files.
2026-02-20 Docs: note successful WLAN loopback validation
    what changed:\n- document in README that WLAN logging mode and WLAN host mode were successfully tested with local loopback using VT100_PTY --autorespond\n- append 2026-02-20 entry in DAILY_CHANGELOG 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
2026-02-20 VT100: integrate WLAN separation architecture into main architecture doc
    Merge WLAN log/host separation model into architecture section 8.3 (session model, data-path gates, telnet policy, lifecycle and command surface).
    Update README and Configuration Guide references to use the architecture document as source of truth.
    Remove obsolete WLAN_Mode_Separation_Plan.md and update DAILY_CHANGELOG for 2026-02-20.
    Validation: make docs in VT100; generated doxygen artifacts reverted.
2026-02-20 VT100: anonymize WLAN template and update release deployment notes
    Anonymize SSID/PSK placeholders in VT100/bin/wpa_supplicant.conf and document release handoff guidance for copying complete VT100/bin to SD with adapted wpa_supplicant.conf.
    Validation: make docs executed; generated doxygen artifacts reverted.
2026-02-22 VT100: keep entered IPv4 order, note prompt/ESC glitches
2026-02-24 VT100: improve VTTest diagnostics and xterm compatibility
    - Add VTTest geometry markers and animated DECOM origin-mode scroll-region demo\n- Improve renderer compatibility for full-screen apps (LNM + xterm alt-screen)\n- Validation: make -j4; VTTest DECOM s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
2026-02-25 VT100: clean local artifacts and update changelog
    - Add local metadata/build artifact ignore rules in VT100/.gitignore\n- Record 2026-02-25 cleanup actions in DAILY_CHANGELOG\n- Preserve existing functional source changes untouched
2026-02-25 VT100: update 2026-02-25 daily changelog
    - consolidate today's functional shell-client integration summary\n- include cleanup and .gitignore hygiene updates in one daily entry
2026-04-21 VT100 AdapterBoard: add TxD level shifter
    Add TxD level shifting network in AdapterBoard schematic and PCB routing.\n\nChanges include new resistor-based shift path and corresponding net/routing updates for TXD signal adaptation.
2026-05-01 README: align VT52/VT100 assessment with hardware scope
    What changed:
    - refocused the conformance assessment on VT52 and VT100 core compatibility
    - documented DECCOLM as out of scope due to fixed display geometry
    - documented DECKPAM/DECKPNM and DECCKM as accepted keyboard/input limitations
    - added a short explanation of application cursor key mode
    - updated DAILY_CHANGELOG for 2026-05-01
2026-05-02 VT100: stabilize VTTest screen resets and summary title
    - reset VTTest intro, frame, and summary screens to a clean full-terminal baseline
    - clear stale DEC line attributes and scroll-region/origin state between special tests
    - normalize the DECOM origin demo to the standard VTTest layout
    - fix summary DWDH title rendering by using line-wide DEC height mode
    - cap the summary DW/DWDH title to 40 characters and avoid unsupported CString precision formatting
    - why:
2026-05-02 VT100: fix setup dialog title and bell rendering
    - render the legacy setup exit hint in double-width underline mode
    - apply the modern setup title ESC#6 sequence on the actual title row
    - mute margin bell only while drawing setup dialogs
    - update the daily changelog for the setup dialog fixes
    - why:
    - make the modern setup title use a real DEC double-width row
2026-05-04 VT100: fix modern setup host_id handling
    Adjust modern setup host_id editing so the first typed character replaces the current value while backspace continues to edit the visible value.
    Suppress screen logger and direct kernel/WLAN host status output while setup dialogs are open so background messages do not paint over configuration screens.
    Correct SaveToFile so host_id and log_output are persisted to their proper configuration keys.
    Validation performed: make -j4 in VT100
2026-05-05 VT100: checkpoint full workspace artifacts
    - capture the current VT100 workspace state including generated artifacts
    - record the latest local Circle submodule checkpoint
    - include rollback release artifacts for targeted recovery
2026-05-06 VT100: fix vttest double-width and DWDH line handling
    - preserve DEC line-size state across CSI 2 K so vttest can rewrite cleared DWDH rows correctly
    - recalculate cursor X when ESC#3/#4/#5/#6 changes the active cell width after CUP
    - clear DW/DWDH rows using active cell width and harden early file logging with immediate startup flush plus visible file I/O error reporting
    - update daily changelog and validate with make -j4
2026-05-06 VT100: improve renderer shadow-buffer projection
    Move more terminal mutations to the shadow buffer and rebuild the visible screen from shadow state, including direct writes, clears, DECALN, and restore paths.
    Add configurable smooth scroll line timing, clamp invalid UART data bits, and route shell-client autostart through host_id with DHCP-aware connect retries.
    Validation: make -j4; hardware runtime check reported noticeably better last-line scroll/autowrap behavior.
2026-05-06 VT100: document shadow-buffer-first renderer architecture
    Clarify that renderer mutations now update shadow state first and treat the framebuffer as a projection target.
    Update the technical architecture document and top-level README to describe the shadow-buffer-first model consistently, and record the documentation change in the daily changelog.
    Validation performed:
    - make docs
2026-05-06 VT100: finalize blink renderer and config guide sync
    Finalize the shadow-buffer blink renderer updates and align the Configuration Guide with the current runtime behavior.
    Document smooth_scroll_ms runtime apply, host_id persistence, and the current WLAN shell-client model, and add the referenced V2.3 hardware schematic/layout image assets used by the hardware document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
    Validation performed:
    - make -j4
    - make docs
2026-05-07 VT100: extract renderer projector into dedicated class
    move framebuffer projection logic behind new CRendererProjector
    keep CTRenderer as facade with thin delegation wrappers
    add dedicated projector header and update daily changelog
    validate with make -j4 in VT100
2026-05-07 VT100: decouple renderer from framebuffer backend
    extract CRendererSurface as framebuffer backend owner
    route renderer flush, color, and display access through surface
    make projector consume shadow state and surface directly
    update architecture docs and daily changelog
    validation: make -j4, make docs, manual vttest 1-4
2026-05-08 VT100: fix VTTest scroll demo line endings
    Switch the VTTest scroll-region demo stream from LF to CRLF so tests 33-35 no longer drift right while new lines are injected into the active scroll region.
    Update the daily changelog for 2026-05-08.
    Validation performed:
    - make -j4 in VT100
    - manual confirmation from user that the bug is fixed
2026-05-21 VT100: restore setup dialog input processing
    - move setup key and raw-key handling into the CTSetup task context
    - stabilize setup task re-entry with Start/Resume lifecycle handling
    - route visible setup input through the kernel setup path
    - keep the daily changelog in sync with the fix
    Validation performed:
    - make -j4 in VT100
2026-05-22 VT100: fix stale-object link failures in build rules
    Fix the active VT100 Makefile compile rules to emit dependency files.
    The previous build path included but did not generate .d files for the active C++, C, and assembler rules. After source and header changes this left stale objects in build/, which caused spurious lin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
    Also align the setup-dialog documentation and shipped VT100.txt templates with the current implementation state.
    Validation performed:
    - make docs
    - make clean && make -j4
2026-05-22 VT100: stabilize setup overlays during smooth scroll
    Abort active smooth scroll state before modal setup overlays take over the screen.
    Defer projector full refresh work until smooth scroll completes when needed, and keep the VT test scroll demo formatting aligned.
    Validation performed:
    - make -j4
2026-05-23 VT100: fix public Circle submodule reference for CI
    Replace the local-only third_party/circle submodule SHA with the nearest public ancestor commit.
    This restores fresh clone and GitHub Actions submodule fetchability without pulling in the newer incompatible Circle API changes.
    Validation performed:
    - verified the referenced Circle commit is reachable on the public remote
    - make -j4

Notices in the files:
VT100/Hardware/AdapterBoard/VT100-V23/VT100-V23.kicad_pcb:
© R. Zühlsdorff
